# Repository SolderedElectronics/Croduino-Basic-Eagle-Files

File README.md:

# Croduino Basic Eagle Files
## Image

[Croduino Basic(100009)](https://e-radionica.com/en/croduino-basic.html)

## Description and details
Croduino Basic is 100% Arduino compatible board made in EU(Croatia), created to promote Arduino culture in Croatia(well, it's named CROduino). Install Arduino software, plug it into USB and start DIY-ing!

It has even more analog inputs than Arduino Uno, features FTDI USB chip and built-in voltage regulator. The main difference from original Arduino and Croduino is size. Croduino is just 5cm x 3cm which makes it very easy to implement into projects. More:

- Atmega328 microcontroller(32kB flash, 2kB RAM, 1kB EEPROM)
- FTDI USB converter
- 22 I/O pins, 14 digital I/O, 6 PWM, 8 analog pins
- Size only 3 x 5cm (1.2 x 2 inch)
- LED light on the 13th pin
- Voltage regulator for possibility of external charging
- Made in Croatia
- Free lifetime technical support at techsupport@e-radionica.com

Microcontroller on-board is loaded with Arduino Optiboot bootloader.

## Repository content
This repo contains Cadsoft Eagle .sch and .brd files for Croduino Basic board. It also contains schematic in .pdf created from .sch Eagle file. 
Files have been arranged into folders for navigating between different versions of board. 
Tip: layer 200 shows top silkscreen and layer 208 should be bottom silkscreen. tParts and bParts is not used.

## Docs
- [Croduino Basic product page] (https://e-radionica.com/en/croduino-basic.html)
- [Croduino lessons - on croatian language] (https://vimeo.com/channels/croduino)

## Board versions
- v1.0 - inital internal version for protyping and internal projects. 
- v1.1 - production run version, some visual details changed.
- v1.2 - current version, never produced. Visual improved even more, few traces optimised. 

## License info
This product is open-source. Yay!
For any tech questions, contact us at techsupport@e-radionica.com
If you find an Issue, please open one at GitHub. If you can improve our product, fork us.

e-radionica.com Team.

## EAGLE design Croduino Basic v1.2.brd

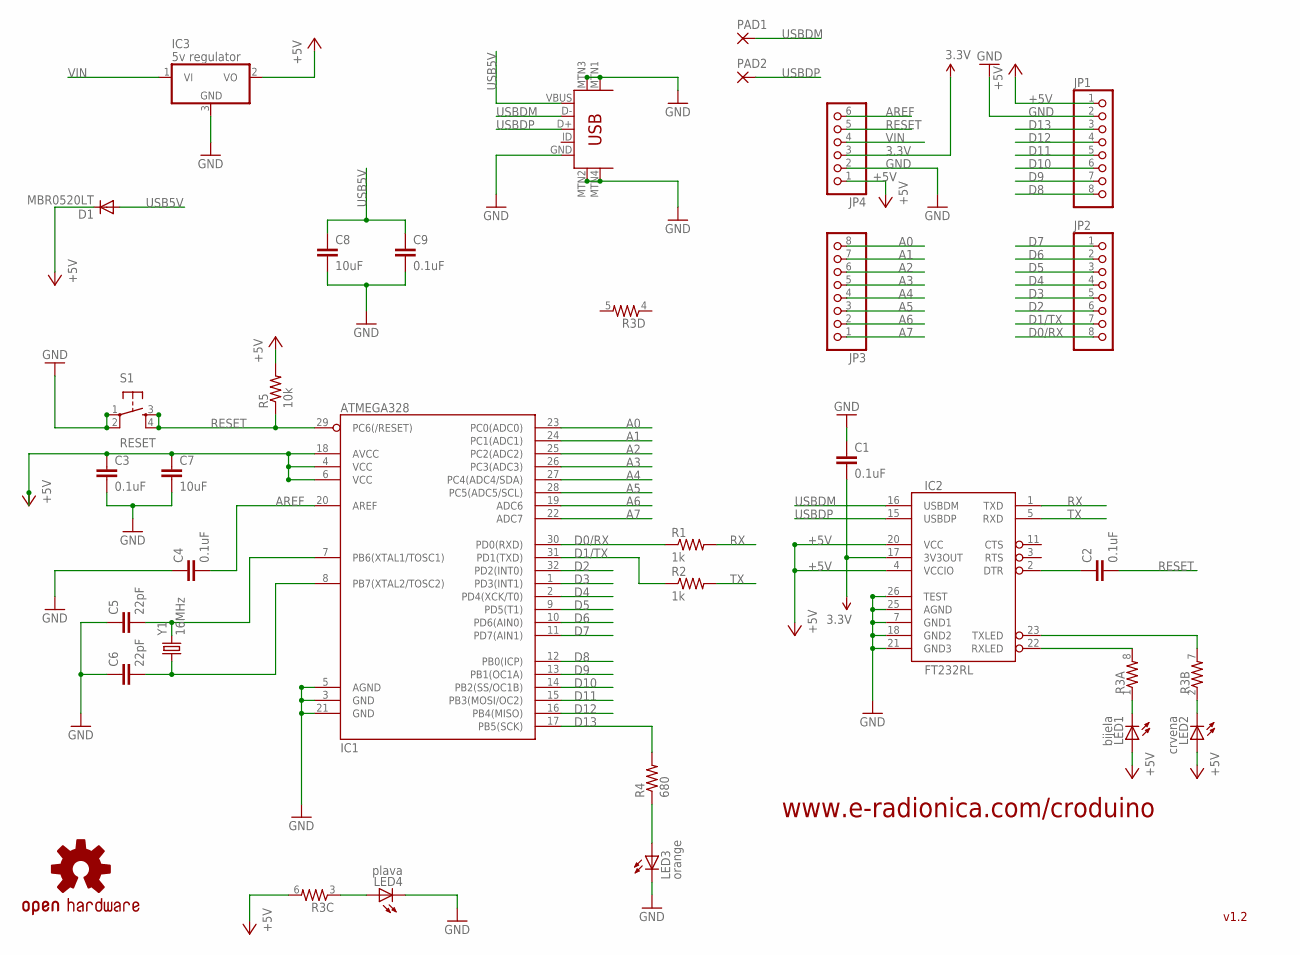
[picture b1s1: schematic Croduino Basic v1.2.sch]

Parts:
C1, C2, C3, C4, C9: 0.1uF; 0603-CAP
C5, C6: 22pF; 0603-CAP
C7, C8: 10uF; C3216
D1: MBR0520LT; SOD123
IC1: ATMEGA328; TQFP32-08
IC2: FT232RL; SSOP28DB
IC3: 5v regulator; TO252
JP1, JP2, JP3: PINHD-1X8BIG; 1X08-BIG
JP4: PINHD-1X6B; 1X06-BIG
LED1: bijela; CHIP-LED0805
LED2: crvena; CHIP-LED0805
LED3: orange; CHIP-LED0805
LED4: plava; CHIP-LED0805
PAD1, PAD2: SMD2; SMD1,27-2,54
R1, R2: 1k; 0603-RES
R3: RESISTOR-ARRAY0603-ARV; 0603-ARV
R4: 680; 0603-RES
R5: 10k; 0603-RES
S1: RESET; TACTILE_SWITCH_SMD
U1: USB-MINIB
U$5: OSHW-LOGOS; OSHW-LOGO-S
Y1: 16MHz; CRYSTAL-SMD-5X3

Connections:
3.3V: C1.2, IC2.17 (3V3OUT), JP4.3
+5V: C3.1, C7.1, D1.C, IC1.4 (VCC), IC1.6 (VCC), IC1.18 (AVCC), IC2.4 (VCCIO), IC2.20 (VCC), IC3.2 (VO), JP1.1, JP4.1, LED1.A, LED2.A, R3.6 (2), R5.2
A0: IC1.23 (PC0(ADC0)), JP3.8
A1: IC1.24 (PC1(ADC1)), JP3.7
A2: IC1.25 (PC2(ADC2)), JP3.6
A3: IC1.26 (PC3(ADC3)), JP3.5
A4: IC1.27 (PC4(ADC4/SDA)), JP3.4
A5: IC1.28 (PC5(ADC5/SCL)), JP3.3
A6: IC1.19 (ADC6), JP3.2
A7: IC1.22 (ADC7), JP3.1
AREF: C4.2, IC1.20 (AREF), JP4.6
CRYSTAL1: C5.2, IC1.7 (PB6(XTAL1/TOSC1)), Y1.3 (2)
CRYSTAL2: C6.2, IC1.8 (PB7(XTAL2/TOSC2)), Y1.1
D0/RX: IC1.30 (PD0(RXD)), JP2.8, R1.1
D1/TX: IC1.31 (PD1(TXD)), JP2.7, R2.1
D2: IC1.32 (PD2(INT0)), JP2.6
D3: IC1.1 (PD3(INT1)), JP2.5
D4: IC1.2 (PD4(XCK/T0)), JP2.4
D5: IC1.9 (PD5(T1)), JP2.3
D6: IC1.10 (PD6(AIN0)), JP2.2
D7: IC1.11 (PD7(AIN1)), JP2.1
D8: IC1.12 (PB0(ICP)), JP1.8
D9: IC1.13 (PB1(OC1A)), JP1.7
D10: IC1.14 (PB2(SS/OC1B)), JP1.6
D11: IC1.15 (PB3(MOSI/OC2)), JP1.5
D12: IC1.16 (PB4(MISO)), JP1.4
D13: IC1.17 (PB5(SCK)), JP1.3, R4.2
GND: C1.1, C3.2, C4.1, C5.1, C6.1, C7.2, C8.2, C9.2, IC1.3 (GND), IC1.5 (AGND), IC1.21 (GND), IC2.7 (GND1), IC2.18 (GND2), IC2.21 (GND3), IC2.25 (AGND), IC2.26 (TEST), IC3.3 (GND), JP1.2, JP4.2, LED3.C, LED4.C, S1.1, S1.2, U1.GND, U1.MTN1 (MTN2), U1.MTN2 (MTN3), U1.MTN3 (MTN1), U1.MTN4
unnamed: LED1.C, R3.1
unnamed: LED2.C, R3.2 (1)
unnamed: C2.1, IC2.2 (DTR)
unnamed: LED3.A, R4.1
unnamed: LED4.A, R3.3 (1)
RESET: C2.2, IC1.29 (PC6(/RESET)), JP4.5, R5.1, S1.3, S1.4
RX: IC2.1 (TXD), R1.2
RXLED: IC2.22 (RXLED), R3.8 (2)
TX: IC2.5 (RXD), R2.2
TXLED: IC2.23 (TXLED), R3.7 (2)
USB5V: C8.1, C9.1, D1.A, U1.VBUS
USBDM: IC2.16 (USBDM), PAD1.1, U1.D-
USBDP: IC2.15 (USBDP), PAD2.1, U1.D+
VIN: IC3.1 (VI), JP4.4

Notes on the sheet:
v1.2
www.e-radionica.com/croduino

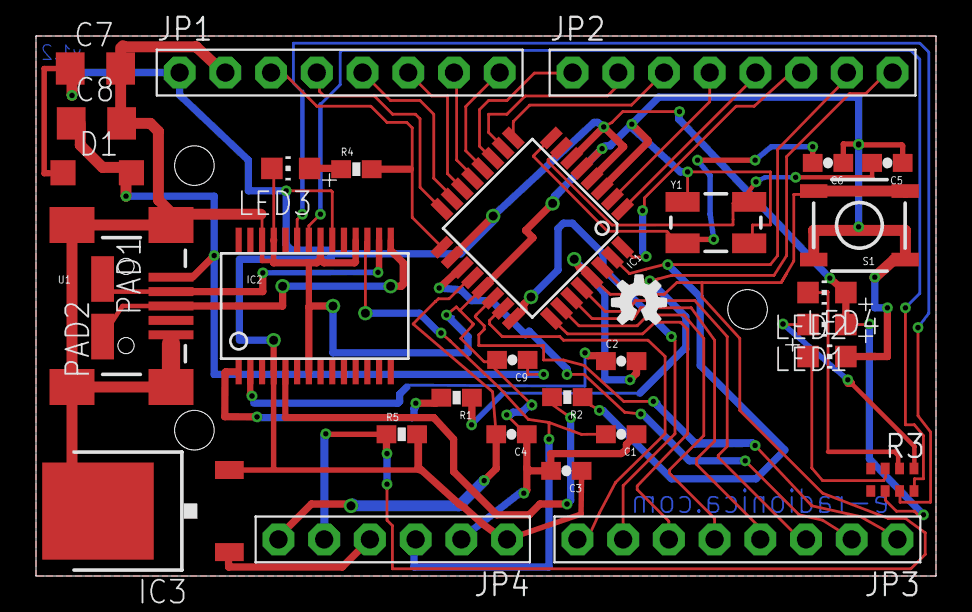
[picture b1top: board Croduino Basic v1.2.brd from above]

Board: 2 copper layers, 50.0 x 30.0 mm, 35 parts (0 on the bottom side), 42 nets.

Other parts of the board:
U$1: CRODUINO_BASIC2
U$2: MADE-IN-CROATIA
U$4: UTICNICA3MM

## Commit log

2015-08-14 Added Eagle files and .pdf Schematic
2015-08-24 Updated Readme and recreated Eagle files
2015-11-03 Typo in README
2016-02-12 README change
    Changed links on e-radionica.com from HTTP to HTTPS since we enabled
    SSL.
2018-11-26 README update

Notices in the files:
parts and their libraries:
SparkFun: Licensing: CC v3.0 Share-Alike You are welcome to use this library for commercial purposes.
